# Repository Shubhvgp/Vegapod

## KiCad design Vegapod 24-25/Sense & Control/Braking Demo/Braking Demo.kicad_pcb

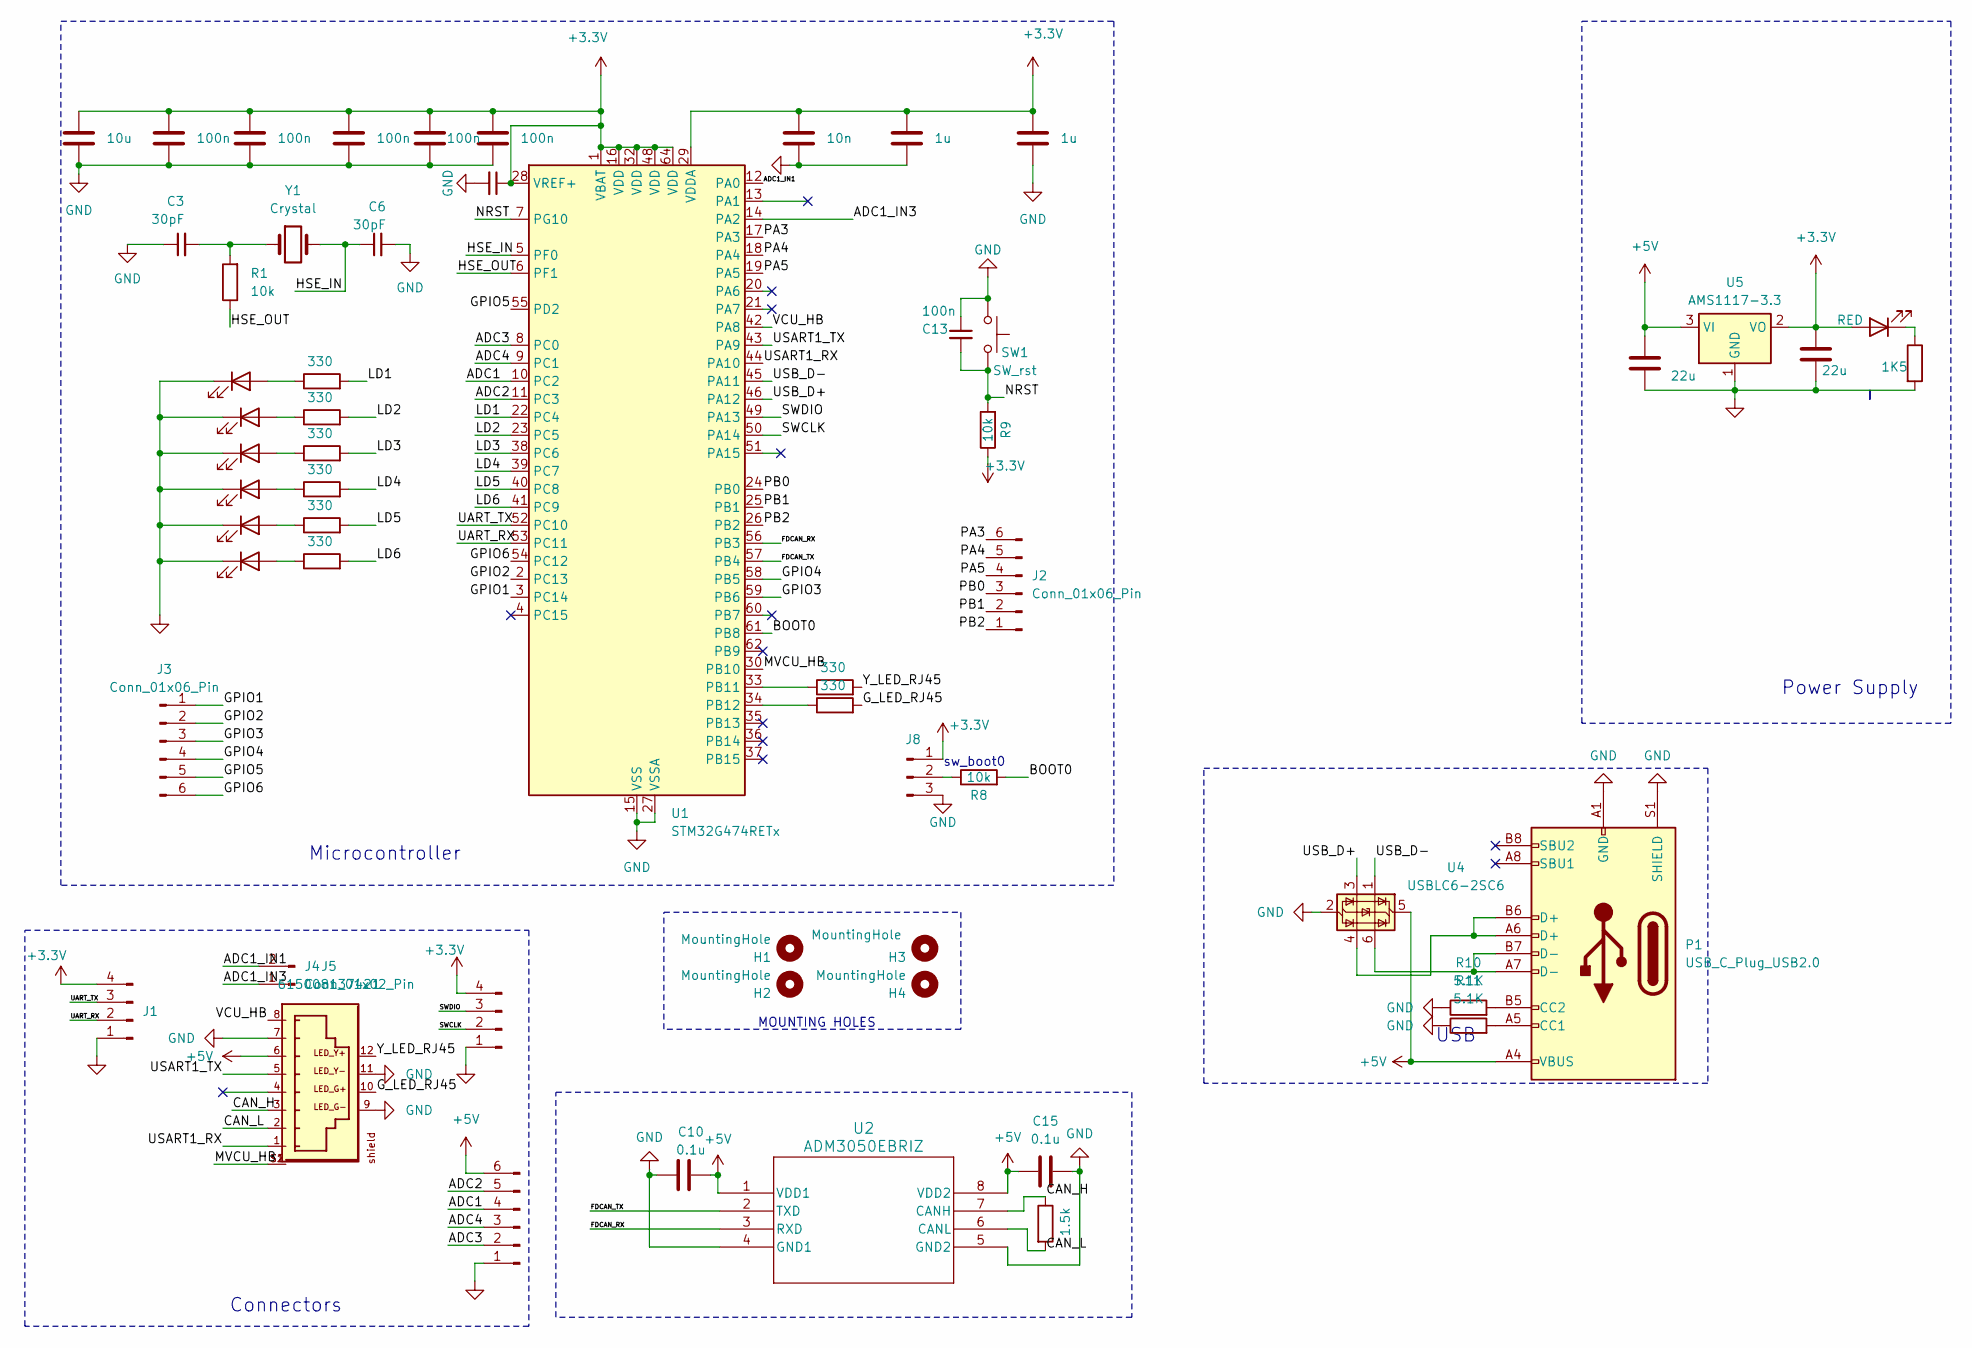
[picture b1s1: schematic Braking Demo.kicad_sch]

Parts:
C1: 10u; C_0805_2012Metric_Pad1.18x1.45mm_HandSolder
C2, C4, C5, C7, C8, C9, C13: 100n; C_0805_2012Metric_Pad1.18x1.45mm_HandSolder
C3, C6: 30pF; C_0805_2012Metric_Pad1.18x1.45mm_HandSolder
C10, C15: 0.1u; C_0805_2012Metric_Pad1.18x1.45mm_HandSolder
C11: 10n; C_0805_2012Metric_Pad1.18x1.45mm_HandSolder
C12, C14: 1u; C_0805_2012Metric_Pad1.18x1.45mm_HandSolder
C18, C19: 22u; C_0805_2012Metric_Pad1.18x1.45mm_HandSolder
D1, D2, D3, D4, D5, D6: LED; LED_0805_2012Metric_Pad1.15x1.40mm_HandSolder
D8: RED; LED_0805_2012Metric_Pad1.15x1.40mm_HandSolder
H1, H2, H3, H4: MountingHole; MountingHole_3.2mm_M3
J1, J6: Conn_01x04_Pin; 4_Pin_686E0422250110E
J2, J3, J7: Conn_01x06_Pin; PinHeader_1x06_P2.54mm_Vertical
J4: Conn_01x02_Pin; PinHeader_1x02_P2.54mm_Vertical
J5: 615008137421; PART-NUMBER 615008137421
J8: Conn_01x03_Pin; PinHeader_1x03_P2.54mm_Vertical
P1: USB_C_Plug_USB2.0; USB_C_Receptacle_GCT_USB4085
R1, R8, R9: 10k; R_0805_2012Metric_Pad1.20x1.40mm_HandSolder
R2, R3, R4, R5, R6, R7, R12, R13: 330; R_0805_2012Metric_Pad1.20x1.40mm_HandSolder
R10, R11: 5.1K; R_0805_2012Metric_Pad1.20x1.40mm_HandSolder
R14: 1.5k; R_0805_2012Metric_Pad1.20x1.40mm_HandSolder
R15: 1K5; R_0805_2012Metric_Pad1.20x1.40mm_HandSolder
SW1: SW_rst; SW_PUSH_6mm_H5mm
U1: STM32G474RETx; LQFP-64_10x10mm_P0.5mm
U2: ADM3050EBRIZ; RI-8-1_ADI
U4: USBLC6-2SC6; SOT-23-6
U5: AMS1117-3.3; SOT-223-3_TabPin2
Y1: Crystal; Crystal_HC49-U_Vertical

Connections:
+3.3V: C1.1, C2.1, C4.1, C5.1, C7.1, C8.1, C9.1, C11.1, C12.1, C14.1, C19.1, D8.2 (A), J1.4, J6.4, J8.1, R9.1, U1.1 (VBAT), U1.16 (VDD), U1.28 (VREF+), U1.29 (VDDA), U1.32 (VDD), U1.48 (VDD), U1.64 (VDD), U5.2 (VO)
+5V: C10.2, C15.2, C18.1, J5.6, J7.6, P1.A4 (VBUS), P1.A9 (VBUS), P1.B4 (VBUS), P1.B9 (VBUS), U2.1 (VDD1), U2.8 (VDD2), U4.5 (VBUS), U5.3 (VI)
/ADC1: J7.4, U1.10 (PC2)
/ADC1_IN1: J4.2, U1.12 (PA0)
/ADC1_IN3: J4.1, U1.14 (PA2)
/ADC2: J7.5, U1.11 (PC3)
/ADC3: J7.2, U1.8 (PC0)
/ADC4: J7.3, U1.9 (PC1)
/BOOT0: R8.2, U1.61 (PB8)
/CAN_H: J5.3, R14.1, U2.7 (CANH)
/CAN_L: J5.2, R14.2, U2.6 (CANL)
/FDCAN_RX: U1.56 (PB3), U2.3 (RXD)
/FDCAN_TX: U1.57 (PB4), U2.2 (TXD)
/GPIO1: J3.1, U1.3 (PC14)
/GPIO2: J3.2, U1.2 (PC13)
/GPIO3: J3.3, U1.59 (PB6)
/GPIO4: J3.4, U1.58 (PB5)
/GPIO5: J3.5, U1.55 (PD2)
/GPIO6: J3.6, U1.54 (PC12)
/G_LED_RJ45: J5.10, R13.2
/HSE_IN: C6.1, U1.5 (PF0), Y1.2
/HSE_OUT: R1.1, U1.6 (PF1)
/LD1: R2.2, U1.22 (PC4)
/LD2: R3.2, U1.23 (PC5)
/LD3: R4.2, U1.38 (PC6)
/LD4: R5.2, U1.39 (PC7)
/LD5: R6.2, U1.40 (PC8)
/LD6: R7.2, U1.41 (PC9)
/MVCU_HB: J5.S1, J5.S2, U1.30 (PB10)
/NRST: C13.2, R9.2, SW1.2, U1.7 (PG10)
/PA3: J2.6, U1.17 (PA3)
/PA4: J2.5, U1.18 (PA4)
/PA5: J2.4, U1.19 (PA5)
/PB0: J2.3, U1.24 (PB0)
/PB1: J2.2, U1.25 (PB1)
/PB2: J2.1, U1.26 (PB2)
/SWCLK: J6.2, U1.50 (PA14)
/SWDIO: J6.3, U1.49 (PA13)
/UART_RX: J1.2, U1.53 (PC11)
/UART_TX: J1.3, U1.52 (PC10)
/USART1_RX: J5.1, U1.44 (PA10)
/USART1_TX: J5.5, U1.43 (PA9)
/USB_D+: U1.46 (PA12), U4.3 (I/O2)
/USB_D-: U1.45 (PA11), U4.1 (I/O1)
/VCU_HB: J5.8, U1.42 (PA8)
/Y_LED_RJ45: J5.12, R12.2
GND: C1.2, C2.2, C3.1, C4.2, C5.2, C6.2, C7.2, C8.2, C9.2, C10.1, C11.2, C12.2, C13.1, C14.2, C15.1, C18.2, C19.2, D1.1 (K), D2.1 (K), D3.1 (K), D4.1 (K), D5.1 (K), D6.1 (K), J1.1, J5.7, J5.9, J5.11, J6.1, J7.1, J8.3, P1.A1 (GND), P1.A12 (GND), P1.B1 (GND), P1.B12 (GND), P1.S1 (SHIELD), R10.1, R11.1, R15.2, SW1.1, U1.15 (VSS), U1.27 (VSSA), U1.31 (VSS), U1.47 (VSS), U1.63 (VSS), U2.4 (GND1), U2.5 (GND2), U4.2 (GND), U5.1 (GND)
unnamed: C3.2, R1.2, Y1.1
unnamed: D1.2 (A), R2.1
unnamed: D2.2 (A), R3.1
unnamed: D3.2 (A), R4.1
unnamed: D4.2 (A), R5.1
unnamed: D5.2 (A), R6.1
unnamed: D6.2 (A), R7.1
unnamed: D8.1 (K), R15.1
unnamed: J8.2, R8.1
unnamed: P1.A5 (CC1), R11.2
unnamed: P1.B5 (CC2), R10.2
unnamed: P1.A6 (D+), P1.B6 (D+), U4.4 (I/O2)
unnamed: P1.A7 (D-), P1.B7 (D-), U4.6 (I/O1)
unnamed: R12.1, U1.33 (PB11)
unnamed: R13.1, U1.34 (PB12)

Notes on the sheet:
Microcontroller
USB
Connectors
Power Supply
MOUNTING HOLES
sw_boot0

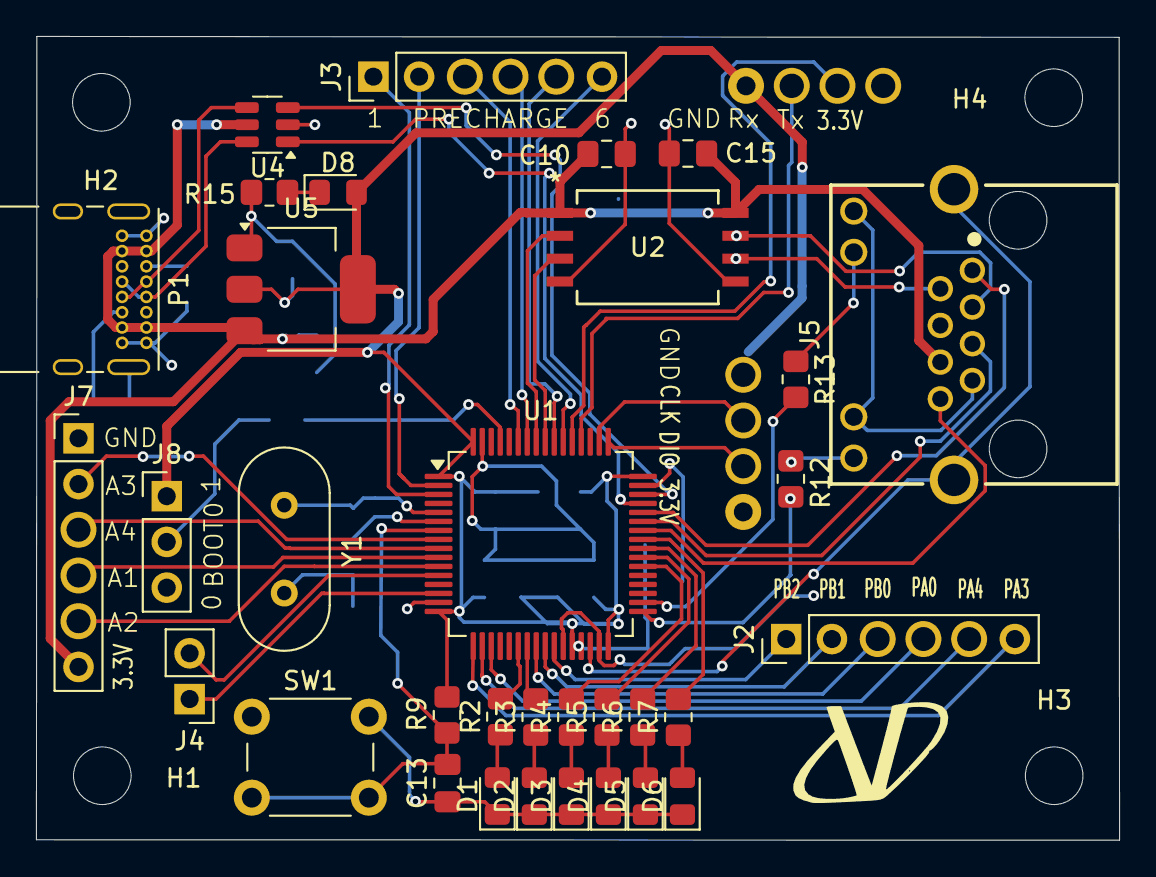
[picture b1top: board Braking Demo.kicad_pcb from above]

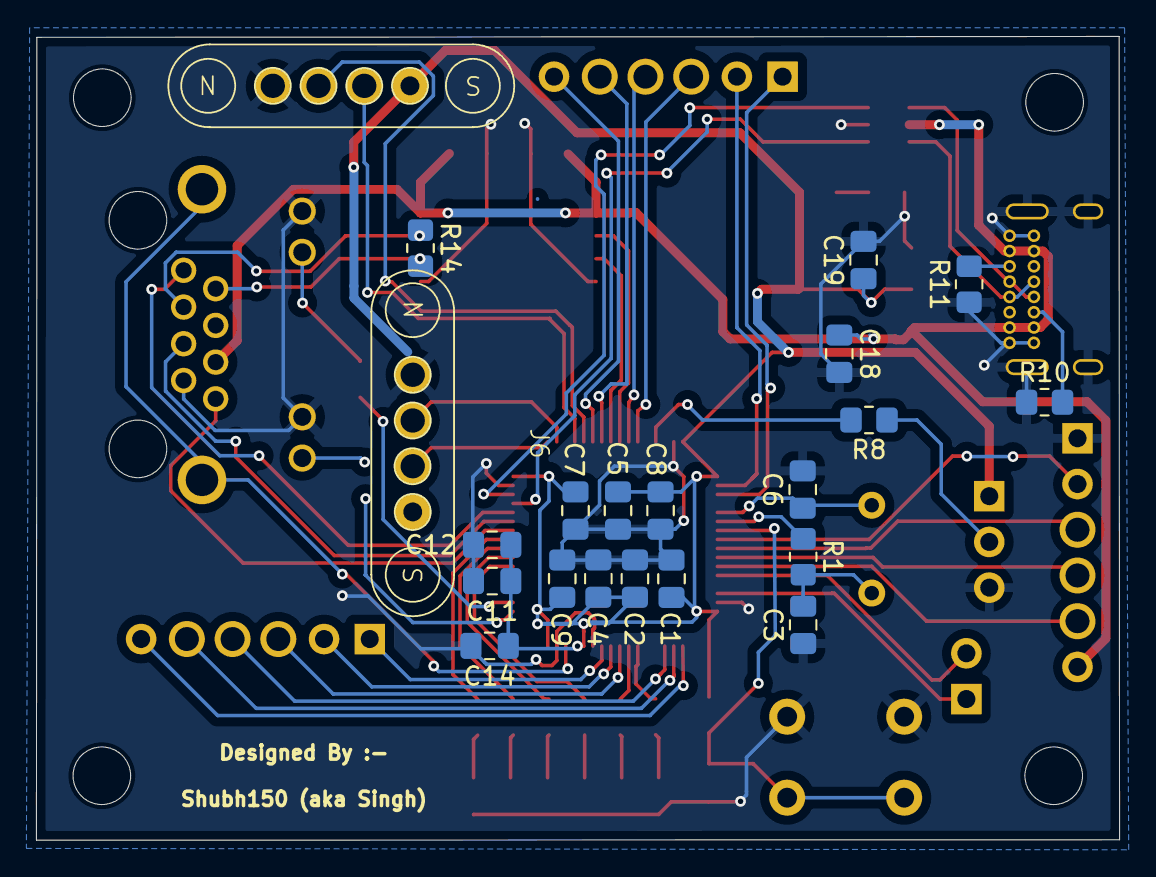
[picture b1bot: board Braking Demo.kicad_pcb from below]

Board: 2 copper layers, 60.2 x 44.7 mm, 58 parts (21 on the bottom side), 62 nets.
